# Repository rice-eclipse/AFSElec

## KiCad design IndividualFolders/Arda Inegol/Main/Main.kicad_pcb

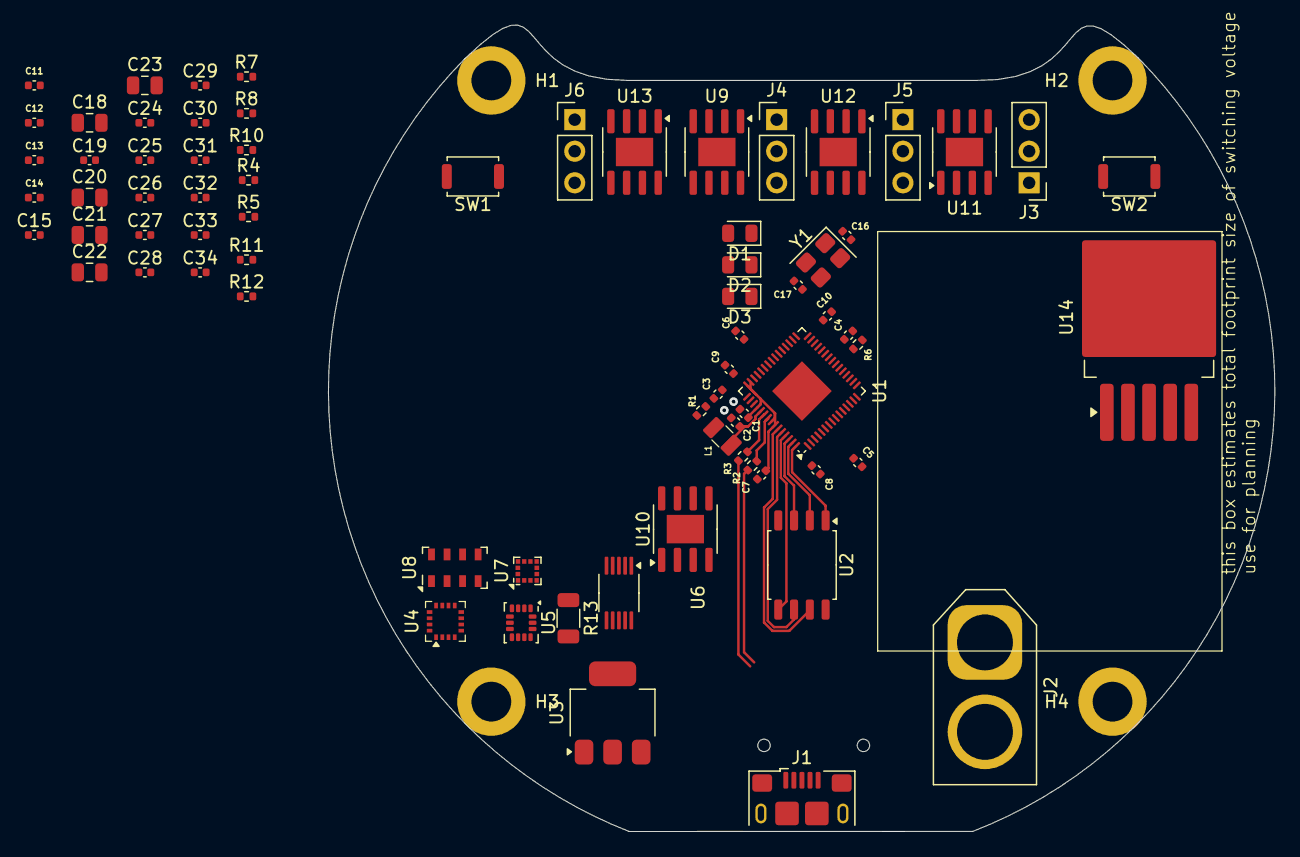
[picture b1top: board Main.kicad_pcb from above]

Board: 4 copper layers, 76.2 x 64.9 mm, 78 parts (1 on the bottom side), 42 nets.

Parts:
C1, C2, C3, C4: 4.7u; C_0402_1005Metric
C5, C6, C7, C8, C9, C10, C11, C12, C13, C14, C15, C19, C24, C25, C26, C27, C28, C29, C30, C31, C32, C33, C34: 100n; C_0402_1005Metric
C16, C17: 15p; C_0402_1005Metric
C18, C20, C21, C23: 10u; C_0805_2012Metric
C22: 1u; C_0805_2012Metric
D1, D2, D3: LED; LED_0805_2012Metric
H1, H2, H3, H4: MountingHole; MountingHole_3.2mm_M3_ISO14580_Pad
J1: USB_B_Micro; USB_Micro-B_Amphenol_10118193-0001LF_Horizontal
J2: Conn_01x02; AMASS_XT60-M_1x02_P7.20mm_Vertical
J3, J4, J5, J6: Conn_01x03; PinHeader_1x03_P2.54mm_Vertical
J7: MSD-4-A; CUI_MSD-4-A
L1: 3.3uH; AOTA-B201610S3R3-101-T(L_0806_2016metric)
R1: 33; R_0402_1005Metric
R2, R3: 22; R_0402_1005Metric
R4, R5, R6: 1k; R_0402_1005Metric
R7, R8: 4.7k; R_0402_1005Metric
R10, R11, R12: R; R_0402_1005Metric
R13: 2m; R_1206_3216Metric
SW1, SW2: SW_Push; SW_Push_SPST_NO_Alps_SKRK
U1: RP2350A-QFN60; QFN-60-1EP_7x7mm_P0.4mm_EP3.4x3.4mm
U2: W25Q128JVS; SOIC-8_5.3x5.3mm_P1.27mm
U3: AMS1117-3.3; SOT-223-3_TabPin2
U4: MMC5983MA; LGA-16_3x3mm_P0.5mm
U5: ICM-42688-P; LGA-14_3x2.5mm_P0.5mm_LayoutBorder3x4y
U6: INA226; VSSOP-10_3x3mm_P0.5mm
U7: KX134-1211; LGA-12_2x2mm_P0.5mm
U8: MS5611-01BA; LGA-8_3x5mm_P1.25mm
U9, U11, U12, U13: MCS1802GS-50-Z; SOIC-8-1EP_3.9x4.9mm_P1.27mm_EP2.29x3mm
U10: LM75B; SOIC-8-1EP_3.9x4.9mm_P1.27mm_EP2.29x3mm
U14: LM2575-3.3BT; TO-263-5_TabPin3
Y1: ABM8-272-T3; Crystal_SMD_3225-4Pin_3.2x2.5mm

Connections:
+1V1: C2.1, C4.1, C5.1, C6.1, L1.1, U1.6 (DVDD), U1.23 (DVDD), U1.39 (DVDD), U1.50 (VREG_FB)
+3.3V: C1.1, C7.1, C8.1, C9.1, C10.1, C11.1, C12.1, C13.1, C14.1, C15.1, C18.1, C19.1, C21.1, C22.2, C24.1, C27.1, C28.1, C29.1, C30.1, C31.1, C32.1, C33.1, C34.1, R1.1, R7.1, R8.1, R10.2, U1.1 (IOVDD), U1.11 (IOVDD), U1.20 (IOVDD), U1.30 (IOVDD), U1.38 (IOVDD), U1.44 (ADC_AVDD), U1.45 (IOVDD), U1.49 (VREG_VIN), U1.53 (USB_OTP_VDD), U1.54 (QSPI_IOVDD), U2.8 (VCC), U3.2 (VO), U4.2 (VDD), U4.13 (VDDIO), U5.2 (RESV_2), U5.3 (RESV_3), U5.5 (VDDIO), U5.8 (VDD), U5.10 (RESV_10), U6.6 (VS), U8.1 (VDD), U9.8 (VCC), U10.8 (+Vs), U11.8 (VCC), U12.8 (VCC), U13.8 (VCC), U14.4 (FB)
/BOOT: R5.1, SW2.2
/QSPI_SCLK: U1.56 (QSPI_SCLK), U2.6 (CLK)
/QSPI_SD0: U1.57 (QSPI_SD0), U2.5 (DI/IO_{0})
/QSPI_SD1: U1.59 (QSPI_SD1), U2.2 (DO/IO_{1})
/QSPI_SD2: U1.58 (QSPI_SD2), U2.3 (~WP/IO_{2})
/QSPI_SD3: U1.55 (QSPI_SD3), U2.7 (~HOLD/~RESET/IO_{3})
/QSPI_SS: R5.2, U1.60 (QSPI_SS), U2.1 (~CS)
/USB+: R2.1, U1.52 (USB_DP)
/USB-: R3.1, U1.51 (USB_DM)
/USB_D+: J1.3 (D+), R2.2
/USB_D-: J1.2 (D-), R3.2
GND: C1.2, C2.2, C3.2, C4.2, C5.2, C6.2, C7.2, C8.2, C9.2, C10.2, C11.2, C12.2, C13.2, C14.2, C15.2, C16.1, C17.1, C18.2, C19.2, C20.2, C21.2, C22.1, C23.2, C24.2, C25.2, C26.1, C27.2, C28.2, C31.2, C32.2, C33.2, C34.2, D1.1 (K), D2.1 (K), D3.1 (K), J1.5 (GND), J1.6 (Shield), J2.1, J3.3, J4.3, J5.3, J6.3, R4.1, R13.1, SW2.1, U1.47 (VREG_PGND), U1.61 (GND), U2.4 (GND), U3.1 (GND), U4.9 (GND), U4.11 (GND), U5.6 (GND), U5.7 (RESV_7), U6.1 (A1), U6.2 (A0), U6.7 (GND), U6.8 (Vbus), U6.9 (Vin-), U7.8 (GND), U7.9 (GND), U8.2 (PS), U8.3 (GND), U9.5 (GND), U10.4 (GND), U10.5 (A2), U10.6 (A1), U10.7 (A0), U11.5 (GND), U12.5 (GND), U13.5 (GND), U14.3 (GND), U14.5 (~ON/OFF), Y1.2, Y1.4
IO_VDD: C25.1, U7.3 (IO_VDD)
MS5611_CS: U8.4 (CSB), U8.5 (CSB)
unnamed: C17.2, R6.1, Y1.3
unnamed: C29.2, C30.2
unnamed: D1.2 (A), R10.1
unnamed: D2.2 (A), R11.1
unnamed: D3.2 (A), R12.1
unnamed: R4.2, SW1.1
unnamed: SW1.2, U1.26 (RUN)
unnamed: C3.1, R1.2, U1.46 (VREG_AVDD)
unnamed: L1.2, U1.48 (VREG_LX)
unnamed: C16.2, U1.21 (XIN), Y1.1
unnamed: R6.2, U1.22 (XOUT)
unnamed: C23.1, U4.10 (CAP)
SCL: R8.2, U6.5 (SCL), U10.2 (SCL)
SDA: R7.2, U6.4 (SDA), U10.1 (SDA)
SPI_SCK: U4.1 (SCL/SPI_SCK), U5.13 (AP_SCL/AP_SCLK), U7.12 (SCLK/SCL)
SPI_SD0: U4.5 (SPI_SDO), U5.1 (AP_SDO/AP_AD0)
SPI_SDI: U4.16 (SDA/SPI_SDI), U5.14 (AP_SDA/AP_SDIO/AP_SDI)
VBUS: C20.1, J1.1 (VBUS), U3.3 (VI)
VDD: C26.2, U7.7 (VDD)
VIN: J2.2, U14.1 (VIN)
VSS: R13.2, U6.10 (Vin+)
current +: U9.3 (IP-), U9.4 (IP-), U11.1 (IP+), U11.2 (IP+), U12.3 (IP-), U12.4 (IP-), U13.1 (IP+), U13.2 (IP+)
current -1: J3.2, U11.3 (IP-), U11.4 (IP-)
current -2: J4.2, U9.1 (IP+), U9.2 (IP+)
current -3: J5.2, U12.1 (IP+), U12.2 (IP+)
current -4: J6.2, U13.3 (IP-), U13.4 (IP-)
